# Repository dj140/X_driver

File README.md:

# X_driver
Base on odrive 3.5 sch

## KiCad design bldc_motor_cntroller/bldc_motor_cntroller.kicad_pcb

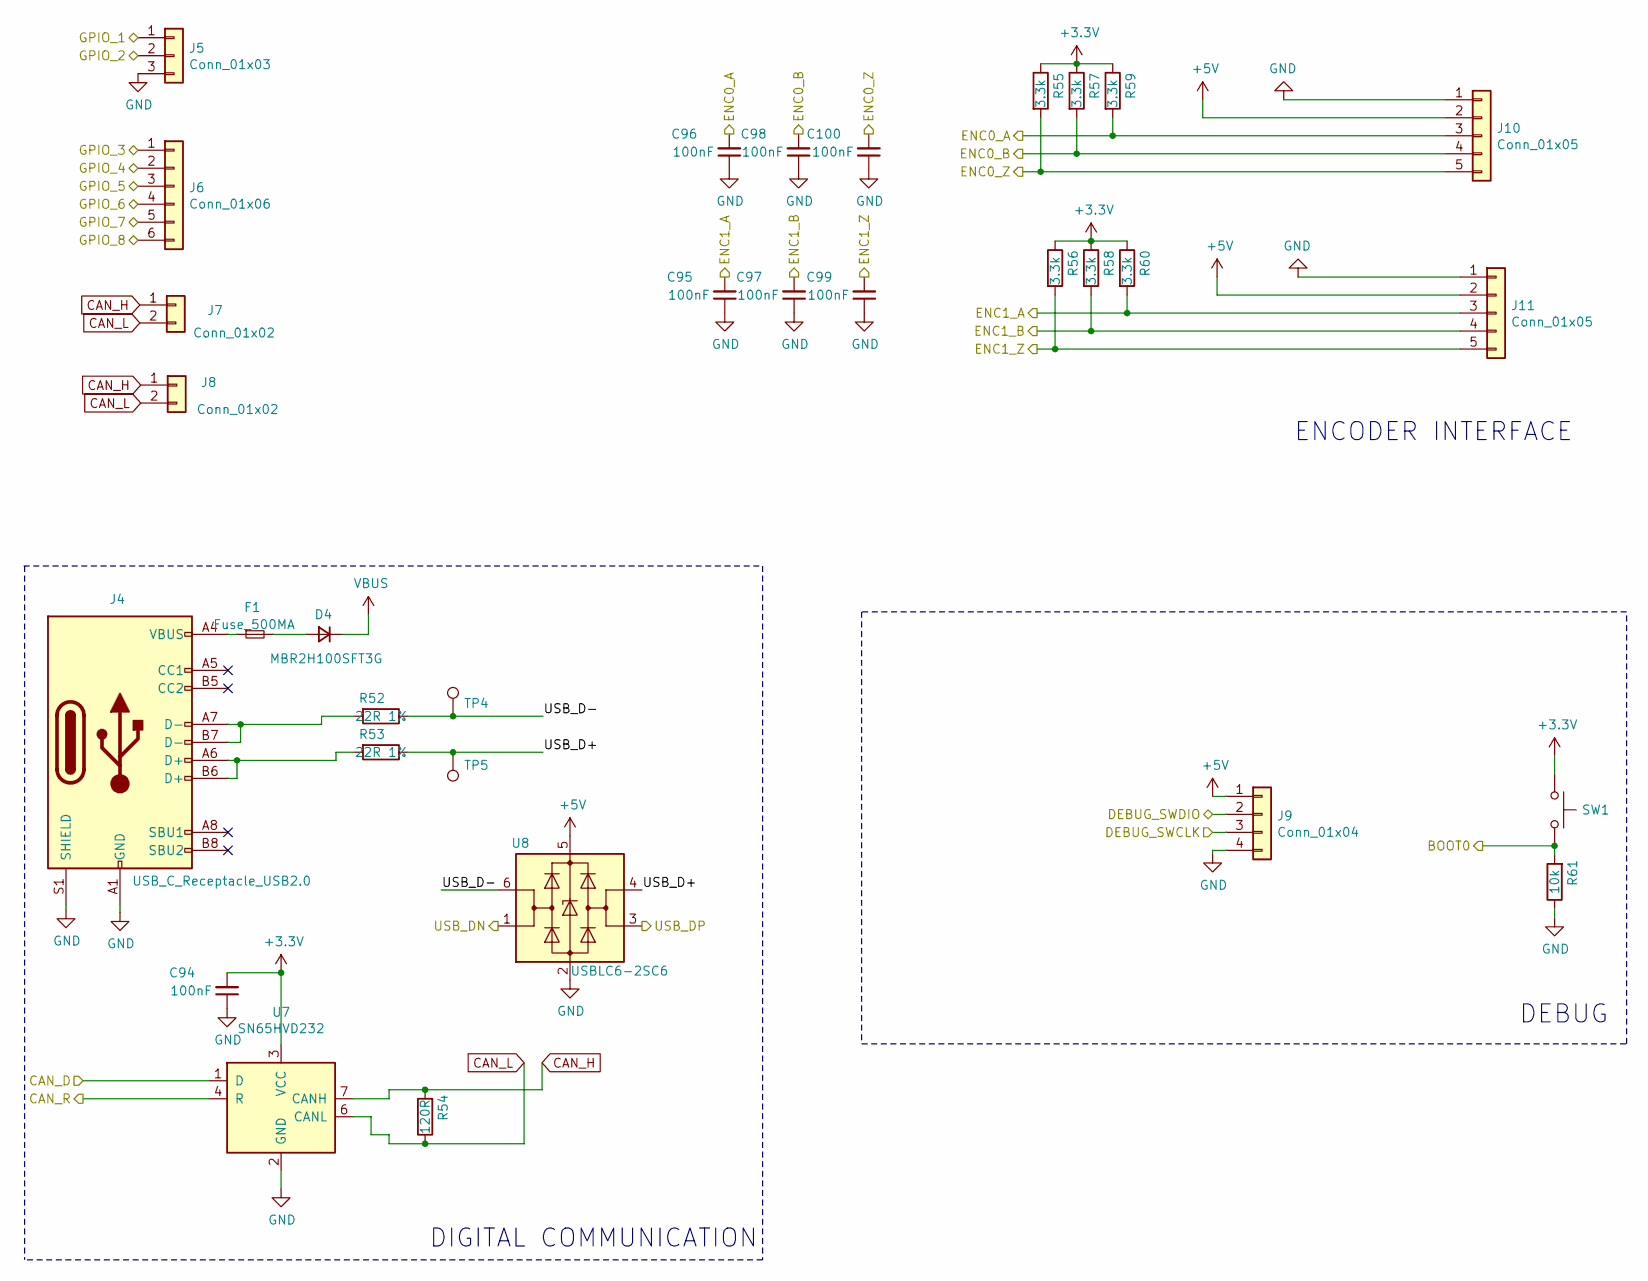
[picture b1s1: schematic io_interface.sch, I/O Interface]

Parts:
C94, C95, C96, C97, C98, C99, C100: 100nF; C_0402_1005Metric; MPN GRM155R62A104KE14D; LCSC Part # C1525
D4: MBR2H100SFT3G; D_SOD-123F
F1: Fuse_500MA; Fuse_1206_3216Metric
J4: USB_C_Receptacle_USB2.0; USB_C_Receptacle_HRO_TYPE-C-31-M-12
J5: Conn_01x03; JST_SH_SM03B-SRSS-TB_1x03-1MP_P1.00mm_Horizontal
J6: Conn_01x06; JST_SH_SM06B-SRSS-TB_1x06-1MP_P1.00mm_Horizontal
J7, J8: Conn_01x02; JST_SH_SM02B-SRSS-TB_1x02-1MP_P1.00mm_Horizontal
J9: Conn_01x04; JST_SH_SM04B-SRSS-TB_1x04-1MP_P1.00mm_Horizontal
J10, J11: Conn_01x05; JST_SH_SM05B-SRSS-TB_1x05-1MP_P1.00mm_Horizontal
R52, R53: 22R 1%; R_0402_1005Metric; MPN CRCW040222R0FKEDC; LCSC Part # C25092
R54: 120R; R_0402_1005Metric; MPN ERJ-2RKF1200X; LCSC Part # C25079
R55, R56, R57, R58, R59, R60: 3.3k; R_0402_1005Metric; MPN CRCW04023K30FKEDC; LCSC Part # C25890
R61: 10k; R_0402_1005Metric; MPN CRCW040210K0FKEDC; LCSC Part # C25744
SW1: B3U-1000P-B; SW_SPST_B3U-1000P; MPN B3U-1000P-B
TP4, TP5: TestPoint; TestPoint_Pad_D1.0mm
U7: SN65HVD232; SOIC-8_3.9x4.9mm_P1.27mm
U8: USBLC6-2SC6; SOT-23-6

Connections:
+3V3: C94.2, R55.1, R56.1, R57.1, R58.1, R59.1, R60.1, SW1.1, U7.3 (VCC); also elsewhere on the board
+5V: D4.1 (K), J9.1, J10.2, J11.2, U8.5 (VBUS); also elsewhere on the board
/I/O Interface/BOOT0: R61.2, SW1.2; also elsewhere on the board
/I/O Interface/CAN_D: U7.1 (D); also elsewhere on the board
/I/O Interface/CAN_R: U7.4 (R); also elsewhere on the board
/I/O Interface/DEBUG_SWCLK: J9.3; also elsewhere on the board
/I/O Interface/DEBUG_SWDIO: J9.2; also elsewhere on the board
/I/O Interface/ENC0_A: C96.2, J10.3, R59.2; also elsewhere on the board
/I/O Interface/ENC0_B: C98.2, J10.4, R57.2; also elsewhere on the board
/I/O Interface/ENC0_Z: C100.2, J10.5, R55.2; also elsewhere on the board
/I/O Interface/ENC1_A: C95.2, J11.3, R60.2; also elsewhere on the board
/I/O Interface/ENC1_B: C97.2, J11.4, R58.2; also elsewhere on the board
/I/O Interface/ENC1_Z: C99.2, J11.5, R56.2; also elsewhere on the board
/I/O Interface/GPIO_1: J5.1; also elsewhere on the board
/I/O Interface/GPIO_2: J5.2; also elsewhere on the board
/I/O Interface/GPIO_3: J6.1; also elsewhere on the board
/I/O Interface/GPIO_4: J6.2; also elsewhere on the board
/I/O Interface/GPIO_5: J6.3; also elsewhere on the board
/I/O Interface/GPIO_6: J6.4; also elsewhere on the board
/I/O Interface/GPIO_7: J6.5; also elsewhere on the board
/I/O Interface/GPIO_8: J6.6; also elsewhere on the board
/I/O Interface/USB_D+: R53.1, TP5.1, U8.4 (I/O2)
/I/O Interface/USB_D-: R52.1, TP4.1, U8.6 (I/O1)
/I/O Interface/USB_DN: U8.1 (I/O1); also elsewhere on the board
/I/O Interface/USB_DP: U8.3 (I/O2); also elsewhere on the board
CAN_H: J7.1, J8.1, R54.2, U7.7 (CANH)
CAN_L: J7.2, J8.2, R54.1, U7.6 (CANL)
GND: C94.1, C95.1, C96.1, C97.1, C98.1, C99.1, C100.1, J4.A1 (GND), J4.A12 (GND), J4.B1 (GND), J4.B12 (GND), J4.S1 (SHIELD), J5.3, J9.4, J10.1, J11.1, R61.1, U7.2 (GND), U8.2 (GND); also elsewhere on the board
unnamed: D4.2 (A), F1.2
unnamed: F1.1, J4.A4 (VBUS), J4.A9 (VBUS), J4.B4 (VBUS), J4.B9 (VBUS)
unnamed: J4.A6 (D+), J4.B6 (D+), R53.2
unnamed: J4.A7 (D-), J4.B7 (D-), R52.2

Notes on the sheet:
DIGITAL COMMUNICATION
DEBUG
ENCODER INTERFACE

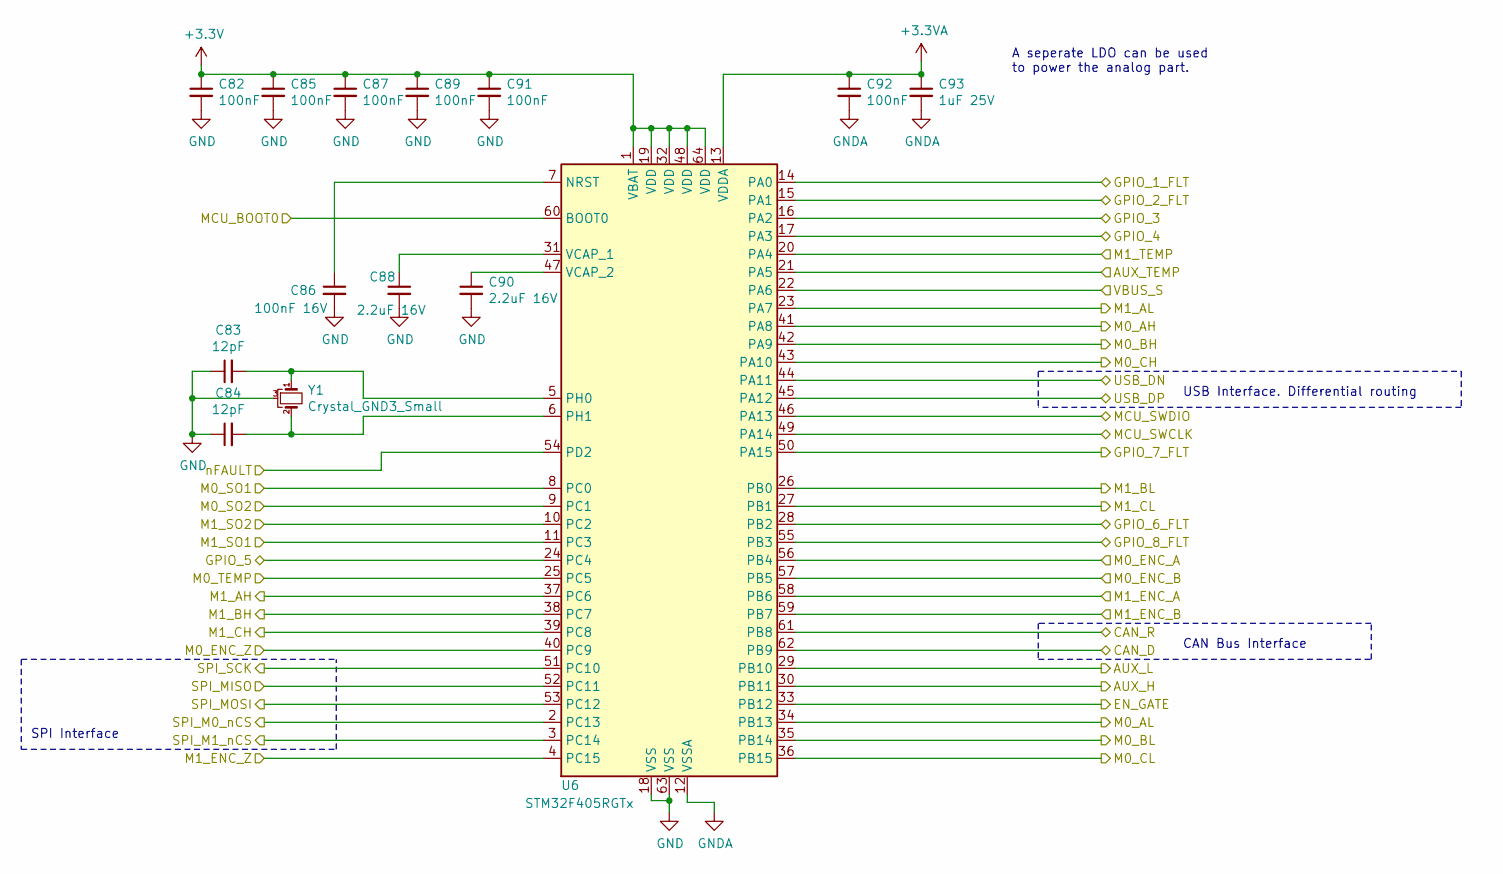
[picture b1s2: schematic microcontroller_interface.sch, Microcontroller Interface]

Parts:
C82, C85, C87, C89, C91, C92: 100nF; C_0402_1005Metric; MPN GRM155R62A104KE14D; LCSC Part # C1525
C83, C84: 12pF; C_0402_1005Metric; MPN GCQ1555C1H120FB01D; LCSC Part # C1547
C86: 100nF 16V; C_0402_1005Metric; MPN GRM155C81E225KE11D; LCSC Part # C1525
C88, C90: 2.2uF 16V; C_0402_1005Metric; MPN GRM155C81E225KE11D
C93: 1uF 25V; C_0402_1005Metric; MPN GMK105CC6105MV-F; LCSC Part # C52923
U6: STM32F405RGTx; LQFP-64_10x10mm_P0.5mm; MPN STM32F405RGT7
Y1: Crystal_GND3_Small; CSTCE8M00G55-R0

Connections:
+3.3VA: C92.1, C93.1, U6.13 (VDDA); also elsewhere on the board
+3V3: C82.1, C85.1, C87.1, C89.1, C91.1, U6.1 (VBAT), U6.19 (VDD), U6.32 (VDD), U6.48 (VDD), U6.64 (VDD); also elsewhere on the board
/I/O Interface/BOOT0: U6.60 (BOOT0); also elsewhere on the board
/I/O Interface/CAN_D: U6.62 (PB9); also elsewhere on the board
/I/O Interface/CAN_R: U6.61 (PB8); also elsewhere on the board
/I/O Interface/DEBUG_SWCLK: U6.49 (PA14); also elsewhere on the board
/I/O Interface/DEBUG_SWDIO: U6.46 (PA13); also elsewhere on the board
/I/O Interface/ENC0_A: U6.56 (PB4); also elsewhere on the board
/I/O Interface/ENC0_B: U6.57 (PB5); also elsewhere on the board
/I/O Interface/ENC0_Z: U6.40 (PC9); also elsewhere on the board
/I/O Interface/ENC1_A: U6.58 (PB6); also elsewhere on the board
/I/O Interface/ENC1_B: U6.59 (PB7); also elsewhere on the board
/I/O Interface/ENC1_Z: U6.4 (PC15); also elsewhere on the board
/I/O Interface/GPIO_1: U6.14 (PA0); also elsewhere on the board
/I/O Interface/GPIO_2: U6.15 (PA1); also elsewhere on the board
/I/O Interface/GPIO_3: U6.16 (PA2); also elsewhere on the board
/I/O Interface/GPIO_4: U6.17 (PA3); also elsewhere on the board
/I/O Interface/GPIO_5: U6.24 (PC4); also elsewhere on the board
/I/O Interface/GPIO_6: U6.28 (PB2); also elsewhere on the board
/I/O Interface/GPIO_7: U6.50 (PA15); also elsewhere on the board
/I/O Interface/GPIO_8: U6.55 (PB3); also elsewhere on the board
/I/O Interface/USB_DN: U6.44 (PA11); also elsewhere on the board
/I/O Interface/USB_DP: U6.45 (PA12); also elsewhere on the board
/Microcontroller Interface/AUX_H: U6.30 (PB11); also elsewhere on the board
/Microcontroller Interface/AUX_L: U6.29 (PB10); also elsewhere on the board
/Microcontroller Interface/AUX_TEMP: U6.21 (PA5); also elsewhere on the board
/Microcontroller Interface/EN_GATE: U6.33 (PB12); also elsewhere on the board
/Microcontroller Interface/M0_AH: U6.41 (PA8); also elsewhere on the board
/Microcontroller Interface/M0_AL: U6.34 (PB13); also elsewhere on the board
/Microcontroller Interface/M0_BH: U6.42 (PA9); also elsewhere on the board
/Microcontroller Interface/M0_BL: U6.35 (PB14); also elsewhere on the board
/Microcontroller Interface/M0_CH: U6.43 (PA10); also elsewhere on the board
/Microcontroller Interface/M0_CL: U6.36 (PB15); also elsewhere on the board
/Microcontroller Interface/M0_TEMP: U6.25 (PC5); also elsewhere on the board
/Microcontroller Interface/M1_AH: U6.37 (PC6); also elsewhere on the board
/Microcontroller Interface/M1_AL: U6.23 (PA7); also elsewhere on the board
/Microcontroller Interface/M1_BH: U6.38 (PC7); also elsewhere on the board
/Microcontroller Interface/M1_BL: U6.26 (PB0); also elsewhere on the board
/Microcontroller Interface/M1_CH: U6.39 (PC8); also elsewhere on the board
/Microcontroller Interface/M1_CL: U6.27 (PB1); also elsewhere on the board
/Microcontroller Interface/M1_TEMP: U6.20 (PA4); also elsewhere on the board
/Microcontroller Interface/SPI_M0_nCS: U6.2 (PC13); also elsewhere on the board
/Microcontroller Interface/SPI_M1_nCS: U6.3 (PC14); also elsewhere on the board
/Microcontroller Interface/SPI_MISO: U6.52 (PC11); also elsewhere on the board
/Microcontroller Interface/SPI_MOSI: U6.53 (PC12); also elsewhere on the board
/Microcontroller Interface/SPI_SCK: U6.51 (PC10); also elsewhere on the board
/Microcontroller Interface/VBUS_S: U6.22 (PA6); also elsewhere on the board
/Microcontroller Interface/nFAULT: U6.54 (PD2); also elsewhere on the board
/Motor Driver/CSENSE_1: U6.8 (PC0); also elsewhere on the board
/Motor Driver/CSENSE_2: U6.9 (PC1); also elsewhere on the board
/Motor_Driver2/CSENSE_1: U6.11 (PC3); also elsewhere on the board
/Motor_Driver2/CSENSE_2: U6.10 (PC2); also elsewhere on the board
GND: C82.2, C83.1, C84.1, C85.2, C86.2, C87.2, C88.2, C89.2, C90.2, C91.2, C92.2, C93.2, U6.12 (VSSA), U6.18 (VSS), U6.63 (VSS), Y1.3; also elsewhere on the board
unnamed: C83.2, U6.5 (PH0), Y1.1
unnamed: C84.2, U6.6 (PH1), Y1.2
unnamed: C86.1, U6.7 (NRST)
unnamed: C88.1, U6.31 (VCAP_1)
unnamed: C90.1, U6.47 (VCAP_2)

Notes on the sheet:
A seperate LDO can be used to power the analog part.
USB Interface. Differential routing
SPI Interface
CAN Bus Interface

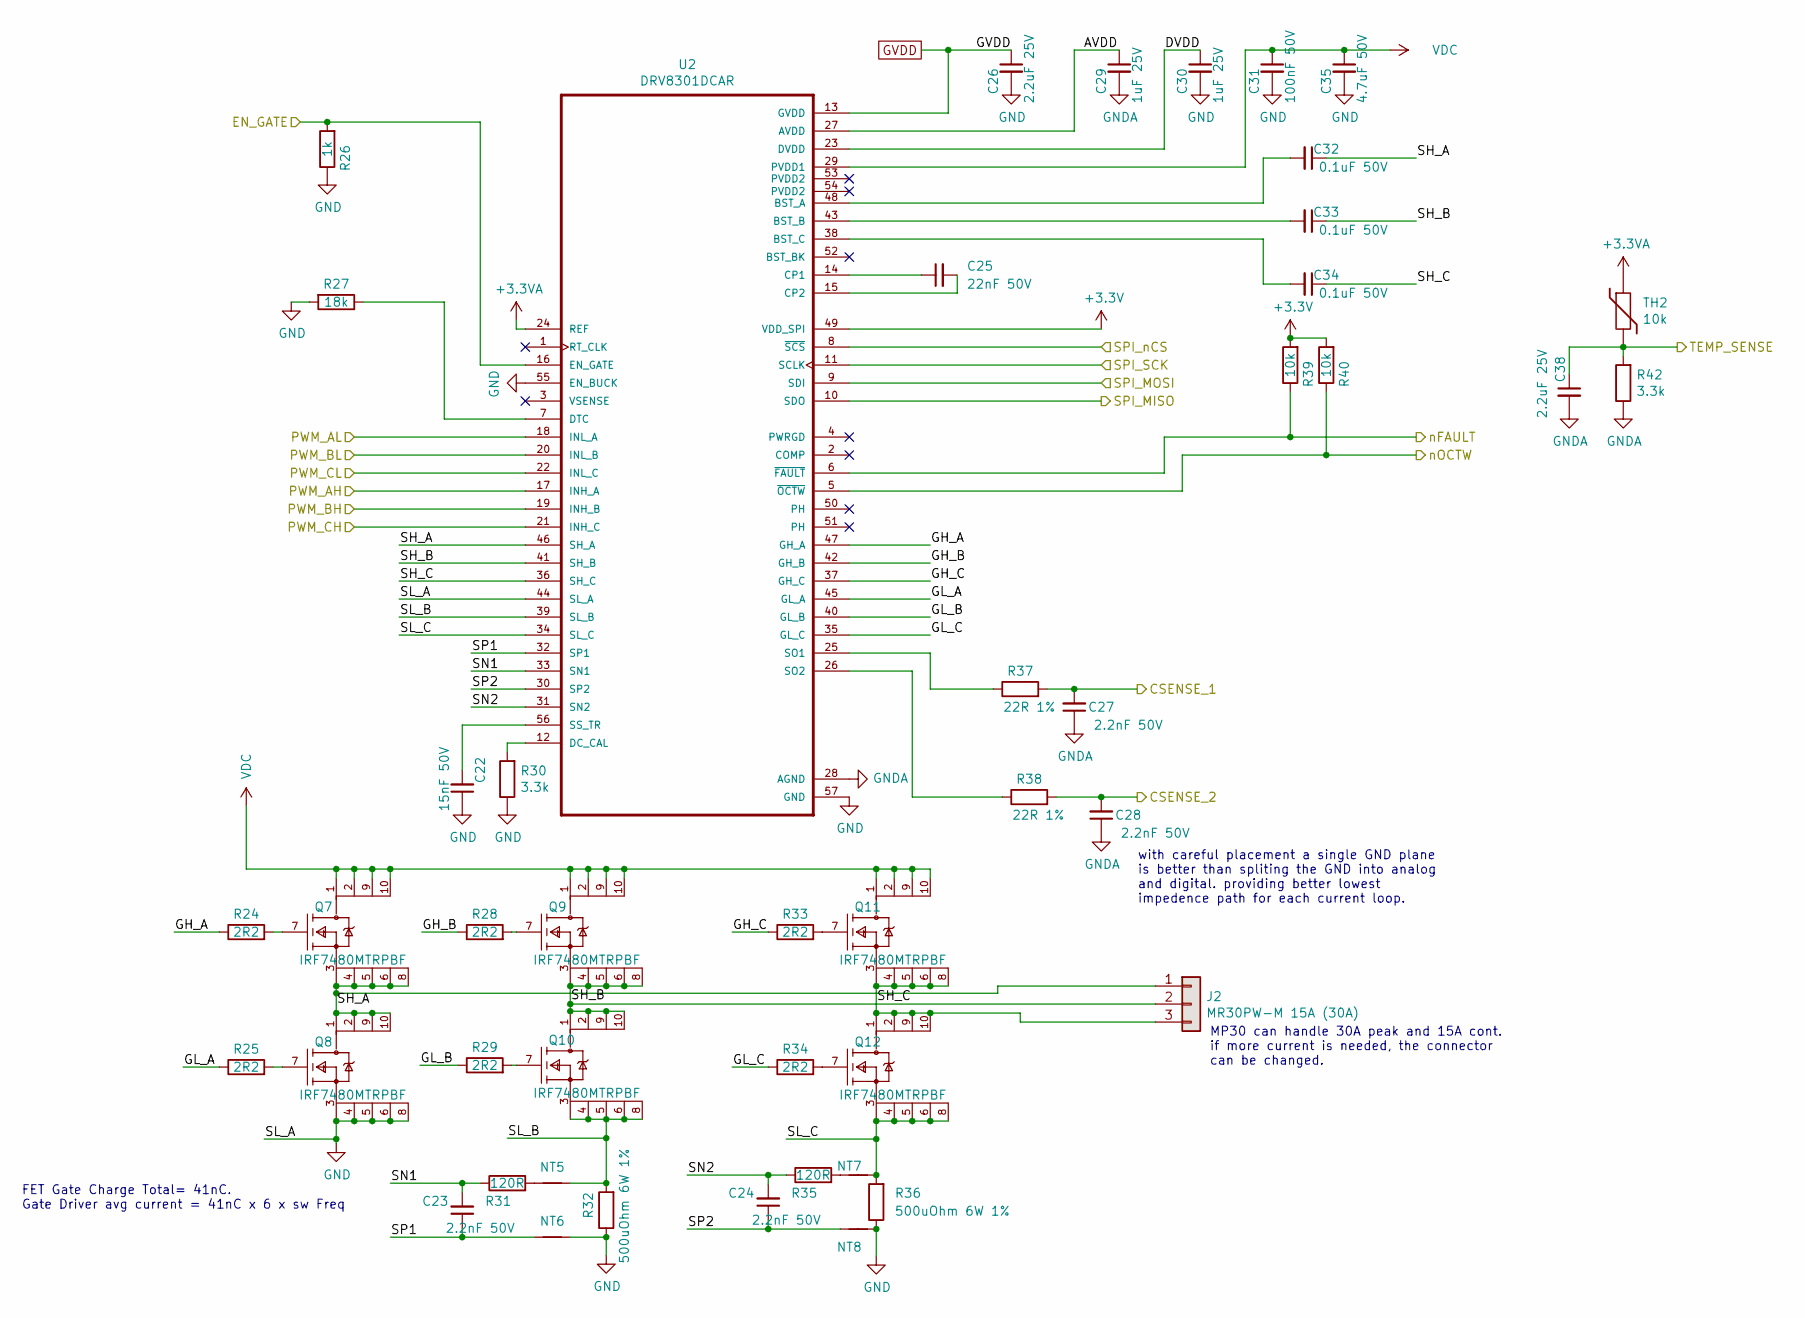
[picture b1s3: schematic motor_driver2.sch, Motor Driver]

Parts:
C22: 15nF 50V; C_0402_1005Metric; MPN GCM155R71E153JA55D
C23, C24, C27, C28: 2.2nF 50V; C_0402_1005Metric; MPN C0402C222J3GEC7411; LCSC Part # C1531
C25: 22nF 50V; C_0402_1005Metric; MPN C0402C223K5REC7411; LCSC Part # C1532
C26, C38: 2.2uF 25V; C_0402_1005Metric; MPN GRM155C81E225KE11D; LCSC Part # C12530
C29, C30: 1uF 25V; C_0402_1005Metric; MPN GMK105CC6105MV-F; LCSC Part # C52923
C31: 100nF 50V; C_0402_1005Metric; MPN GRM155R62A104KE14D
C32, C33, C34: 0.1uF 50V; C_0402_1005Metric; MPN GCM155L8EH104KE07D
C35: 4.7uF 50V; C_1206_3216Metric; MPN HMK325C7475KN-TE
J2: MR30PW-M 15A (30A); AMASS_MR30PW-M_1x03_P3.50mm_Horizontal
NT5, NT6, NT7, NT8: Net-Tie_2; NetTie-2_SMD_Pad0.5mm
Q7, Q8, Q9, Q10, Q11, Q12: IRF7480MTRPBF; Infineon-MG-WDSON-8-05_2016-901-MFG; mouser part number 942-IRF7480MTRPBF; digikey description MOSFET N-CH 40V 217A DIRECTFET
R24, R25, R28, R29, R33, R34: 2R2; R_0402_1005Metric; MPN CRCW04022R20FKEDC
R26: 1k; R_0402_1005Metric; MPN ERJ-2RKF1001X; LCSC Part # C11702
R27: 18k; R_0402_1005Metric; MPN CRCW040218K0FKED; LCSC Part # C25762
R30, R42: 3.3k; R_0402_1005Metric; MPN CRCW04023K30FKEDC; LCSC Part # C25890
R31, R35: 120R; R_0402_1005Metric; MPN ERJ-2RKF1200X; LCSC Part # C25079
R32, R36: 500uOhm 6W 1%; R_2512_6332Metric; MPN CSS2H-2512R-L500F
R37, R38: 22R 1%; R_0402_1005Metric; MPN CRCW040222R0FKEDC; LCSC Part # C25092
R39, R40: 10k; R_0402_1005Metric; MPN CRCW040210K0FKEDC; LCSC Part # C25744
TH2: 10k; R_0402_1005Metric; MPN CRCW040210K0FKEDC
U2: DRV8301DCAR; DRV8301DCA; MPN DRV8301DCAR

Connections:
+3.3VA: TH2.1, U2.24 (REF); also elsewhere on the board
+3V3: R39.2, R40.2, U2.49 (VDD_SPI); also elsewhere on the board
/Microcontroller Interface/EN_GATE: R26.2, U2.16 (EN_GATE); also elsewhere on the board
/Microcontroller Interface/M1_AH: U2.17 (INH_A); also elsewhere on the board
/Microcontroller Interface/M1_AL: U2.18 (INL_A); also elsewhere on the board
/Microcontroller Interface/M1_BH: U2.19 (INH_B); also elsewhere on the board
/Microcontroller Interface/M1_BL: U2.20 (INL_B); also elsewhere on the board
/Microcontroller Interface/M1_CH: U2.21 (INH_C); also elsewhere on the board
/Microcontroller Interface/M1_CL: U2.22 (INL_C); also elsewhere on the board
/Microcontroller Interface/M1_TEMP: C38.1, R42.2, TH2.2; also elsewhere on the board
/Microcontroller Interface/SPI_M1_nCS: U2.8 (~SCS~); also elsewhere on the board
/Microcontroller Interface/SPI_MISO: U2.10 (SDO); also elsewhere on the board
/Microcontroller Interface/SPI_MOSI: U2.9 (SDI); also elsewhere on the board
/Microcontroller Interface/SPI_SCK: U2.11 (SCLK); also elsewhere on the board
/Microcontroller Interface/nFAULT: R39.1, U2.6 (~FAULT~); also elsewhere on the board
/Motor_Driver2/AVDD: C29.1, U2.27 (AVDD)
/Motor_Driver2/CSENSE_1: C27.2, R37.2; also elsewhere on the board
/Motor_Driver2/CSENSE_2: C28.2, R38.2; also elsewhere on the board
/Motor_Driver2/DVDD: C30.1, U2.23 (DVDD)
/Motor_Driver2/GH_A: R24.1, U2.47 (GH_A)
/Motor_Driver2/GH_B: R28.1, U2.42 (GH_B)
/Motor_Driver2/GH_C: R33.1, U2.37 (GH_C)
/Motor_Driver2/GL_A: R25.1, U2.45 (GL_A)
/Motor_Driver2/GL_B: R29.1, U2.40 (GL_B)
/Motor_Driver2/GL_C: R34.1, U2.35 (GL_C)
/Motor_Driver2/SH_A: C32.1, J2.1, Q7.3 (S), Q7.4 (S), Q7.5 (S), Q7.6 (S), Q7.8 (S), Q8.1 (D), Q8.2 (D), Q8.9 (D), Q8.10 (D), U2.46 (SH_A)
/Motor_Driver2/SH_B: C33.1, J2.2, Q9.3 (S), Q9.4 (S), Q9.5 (S), Q9.6 (S), Q9.8 (S), Q10.1 (D), Q10.2 (D), Q10.9 (D), Q10.10 (D), U2.41 (SH_B)
/Motor_Driver2/SH_C: C34.1, J2.3, Q11.3 (S), Q11.4 (S), Q11.5 (S), Q11.6 (S), Q11.8 (S), Q12.1 (D), Q12.2 (D), Q12.9 (D), Q12.10 (D), U2.36 (SH_C)
/Motor_Driver2/SL_B: NT5.2, Q10.3 (S), Q10.4 (S), Q10.5 (S), Q10.6 (S), Q10.8 (S), R32.2, U2.39 (SL_B)
/Motor_Driver2/SL_C: NT7.2, Q12.3 (S), Q12.4 (S), Q12.5 (S), Q12.6 (S), Q12.8 (S), R36.2, U2.34 (SL_C)
/Motor_Driver2/SN1: C23.2, R31.1, U2.33 (SN1)
/Motor_Driver2/SN2: C24.2, R35.1, U2.31 (SN2)
/Motor_Driver2/SP1: C23.1, NT6.1, U2.32 (SP1)
/Motor_Driver2/SP2: C24.1, NT8.1, U2.30 (SP2)
/Motor_Driver2/nOCTW: R40.1, U2.5 (~OCTW~)
GND: C22.1, C26.2, C27.1, C28.1, C29.2, C30.2, C31.2, C35.2, C38.2, NT6.2, NT8.2, Q8.3 (S), Q8.4 (S), Q8.5 (S), Q8.6 (S), Q8.8 (S), R26.1, R27.2, R30.1, R32.1, R36.1, R42.1, U2.28 (AGND), U2.44 (SL_A), U2.55 (EN_BUCK), U2.57 (GND), U2.V; also elsewhere on the board
GVDD: C26.1, U2.13 (GVDD); also elsewhere on the board
unnamed: C22.2, U2.56 (SS_TR)
unnamed: C25.1, U2.14 (CP1)
unnamed: C25.2, U2.15 (CP2)
unnamed: C32.2, U2.48 (BST_A)
unnamed: C33.2, U2.43 (BST_B)
unnamed: C34.2, U2.38 (BST_C)
unnamed: NT5.1, R31.2
unnamed: NT7.1, R35.2
unnamed: Q7.7 (G), R24.2
unnamed: Q8.7 (G), R25.2
unnamed: Q9.7 (G), R28.2
unnamed: Q10.7 (G), R29.2
unnamed: Q11.7 (G), R33.2
unnamed: Q12.7 (G), R34.2
unnamed: R27.1, U2.7 (DTC)
unnamed: R30.2, U2.12 (DC_CAL)
unnamed: R37.1, U2.25 (SO1)
unnamed: R38.1, U2.26 (SO2)
VDC: C31.1, C35.1, Q7.1 (D), Q7.2 (D), Q7.9 (D), Q7.10 (D), Q9.1 (D), Q9.2 (D), Q9.9 (D), Q9.10 (D), Q11.1 (D), Q11.2 (D), Q11.9 (D), Q11.10 (D), U2.29 (PVDD1); also elsewhere on the board

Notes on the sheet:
with careful placement a single GND plane is better than spliting the GND into analog and digital. providing better lowest impedence path for each current loop.
FET Gate Charge Total= 41nC. Gate Driver avg current = 41nC x 6 x sw Freq
MP30 can handle 30A peak and 15A cont. if more current is needed, the connector can be changed.

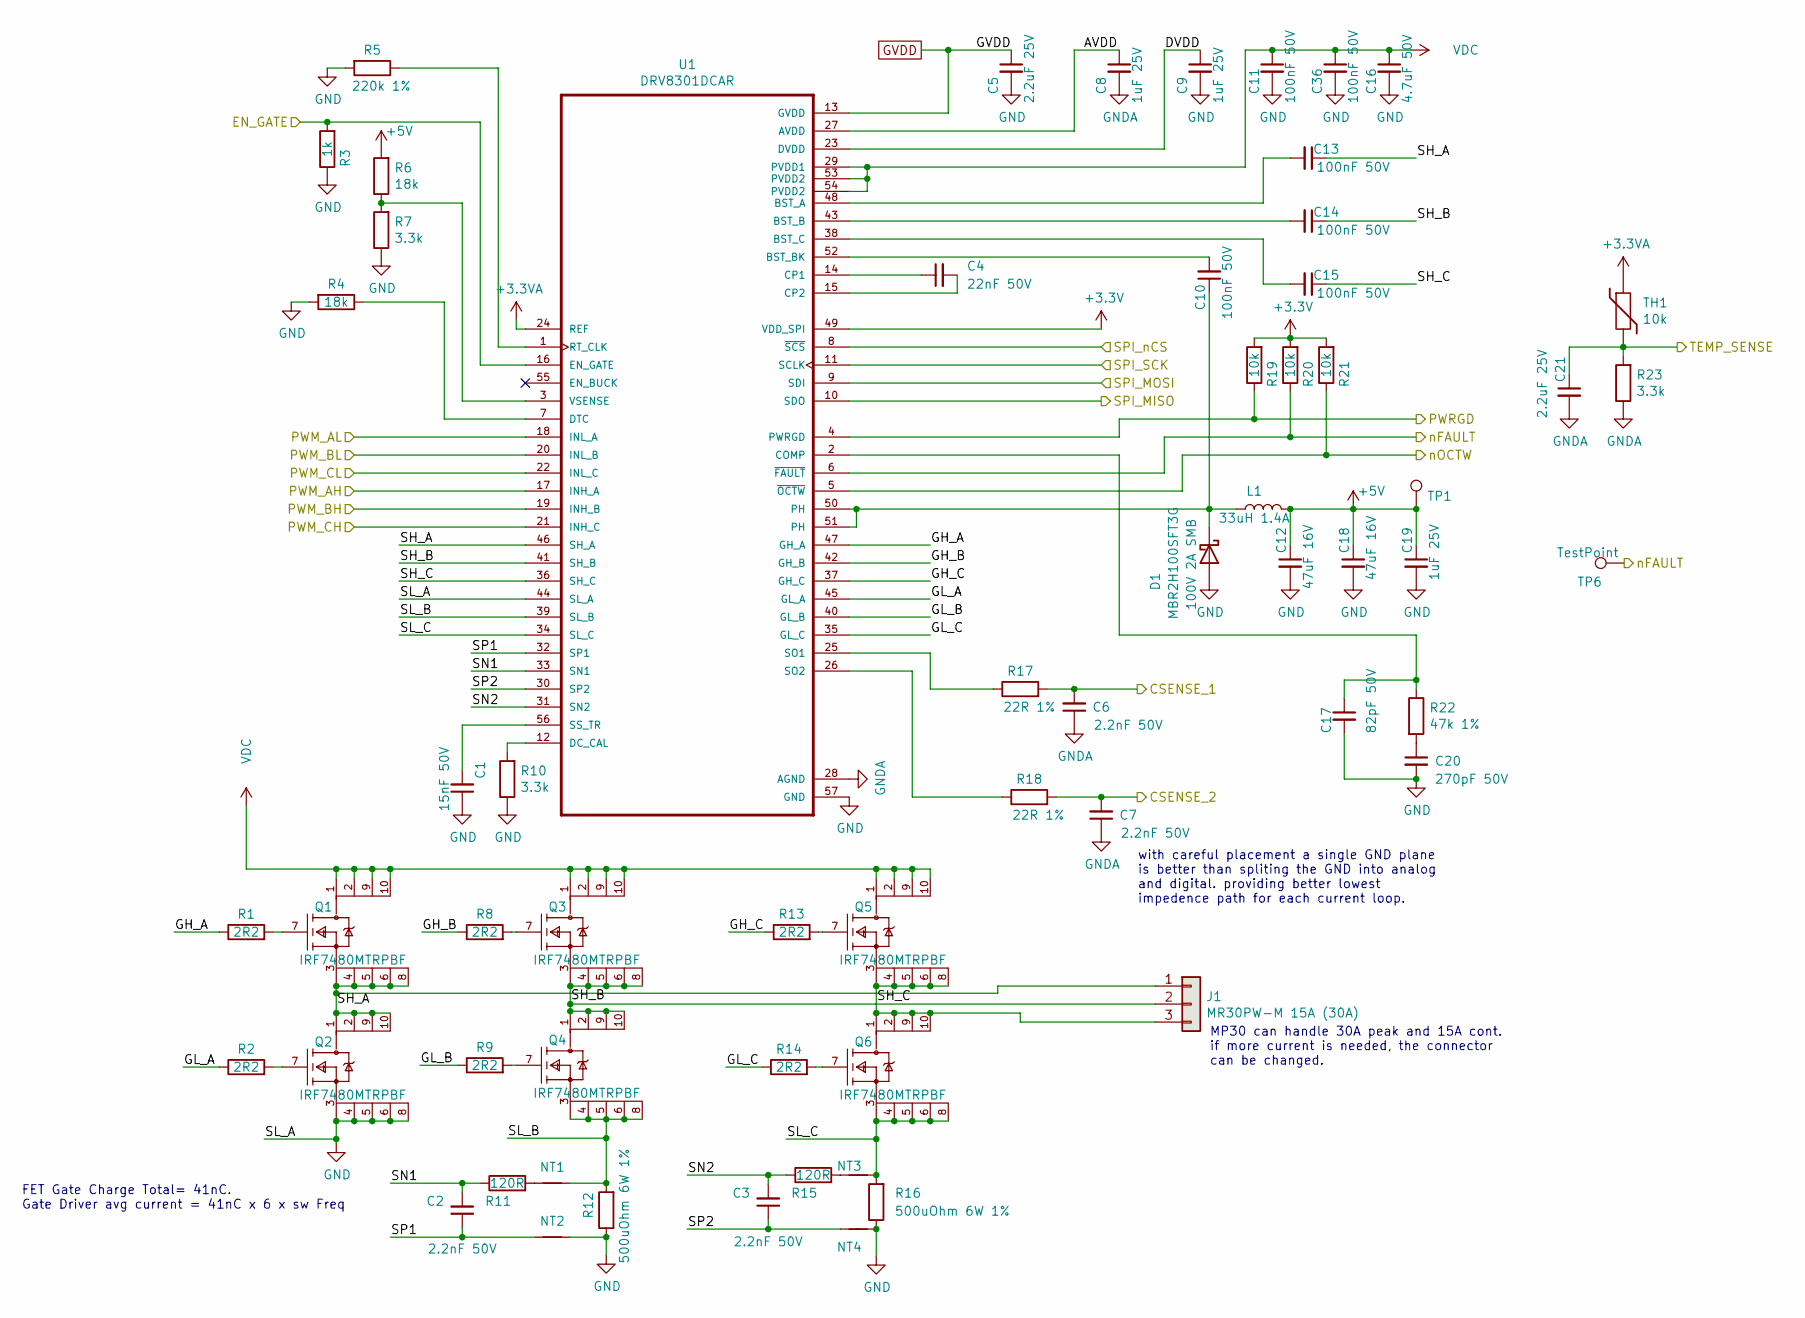
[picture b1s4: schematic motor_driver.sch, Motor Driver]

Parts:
C1: 15nF 50V; C_0402_1005Metric; MPN GCM155R71E153JA55D
C2, C3, C6, C7: 2.2nF 50V; C_0402_1005Metric; MPN C0402C222J3GEC7411; LCSC Part # C1531
C4: 22nF 50V; C_0402_1005Metric; MPN C0402C223K5REC7411; LCSC Part # C1532
C5, C21: 2.2uF 25V; C_0402_1005Metric; MPN GRM155C81E225KE11D; LCSC Part # C12530
C8, C9, C19: 1uF 25V; C_0402_1005Metric; MPN GMK105CC6105MV-F; LCSC Part # C52923
C10, C13, C14, C15: 100nF 50V; C_0402_1005Metric; MPN GCM155L8EH104KE07D
C11, C36: 100nF 50V; C_0402_1005Metric; MPN GRM155R62A104KE14D
C12, C18: 47uF 16V; C_1206_3216Metric; MPN GRM32EC81C476KE15L; LCSC Part # C96123
C16: 4.7uF 50V; C_1206_3216Metric; MPN HMK325C7475KN-TE
C17: 82pF 50V; C_0402_1005Metric; MPN VJ0402A820JXACW1BC
C20: 270pF 50V; C_0402_1005Metric; MPN GRM1555C1H271FA01D
D1: 100V 2A SMB; D_SOD-123F; MPN MBR2H100SFT3G
J1: MR30PW-M 15A (30A); AMASS_MR30PW-M_1x03_P3.50mm_Horizontal
L1: 33uH 1.4A; L_Taiyo-Yuden_NR-60xx; MPN NR6045T330M
NT1, NT2, NT3, NT4: Net-Tie_2; NetTie-2_SMD_Pad0.5mm
Q1, Q2, Q3, Q4, Q5, Q6: IRF7480MTRPBF; Infineon-MG-WDSON-8-05_2016-901-MFG; mouser part number 942-IRF7480MTRPBF; digikey description MOSFET N-CH 40V 217A DIRECTFET
R1, R2, R8, R9, R13, R14: 2R2; R_0402_1005Metric; MPN CRCW04022R20FKEDC
R3: 1k; R_0402_1005Metric; MPN ERJ-2RKF1001X; LCSC Part # C11702
R4, R6: 18k; R_0402_1005Metric; MPN CRCW040218K0FKED; LCSC Part # C25762
R5: 220k 1%; R_0402_1005Metric; MPN CRCW0402220KFKEDC; LCSC Part # C25767
R7, R10, R23: 3.3k; R_0402_1005Metric; MPN CRCW04023K30FKEDC; LCSC Part # C25890
R11, R15: 120R; R_0402_1005Metric; MPN ERJ-2RKF1200X; LCSC Part # C25079
R12, R16: 500uOhm 6W 1%; R_2512_6332Metric; MPN CSS2H-2512R-L500F
R17, R18: 22R 1%; R_0402_1005Metric; MPN CRCW040222R0FKEDC; LCSC Part # C25092
R19, R20, R21: 10k; R_0402_1005Metric; MPN CRCW040210K0FKEDC; LCSC Part # C25744
R22: 47k 1%; R_0402_1005Metric; MPN CRGP0402F47K; LCSC Part # C25792
TH1: 10k; R_0402_1005Metric; MPN CRCW040210K0FKEDC
TP1, TP6: TestPoint; TestPoint_Pad_D1.0mm
U1: DRV8301DCAR; DRV8301DCA; MPN DRV8301DCAR

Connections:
+3.3VA: TH1.1, U1.24 (REF); also elsewhere on the board
+3V3: R19.2, R20.2, R21.2, U1.49 (VDD_SPI); also elsewhere on the board
+5V: C12.1, C18.1, C19.1, L1.2, R6.2, TP1.1; also elsewhere on the board
/Microcontroller Interface/EN_GATE: R3.2, U1.16 (EN_GATE); also elsewhere on the board
/Microcontroller Interface/M0_AH: U1.17 (INH_A); also elsewhere on the board
/Microcontroller Interface/M0_AL: U1.18 (INL_A); also elsewhere on the board
/Microcontroller Interface/M0_BH: U1.19 (INH_B); also elsewhere on the board
/Microcontroller Interface/M0_BL: U1.20 (INL_B); also elsewhere on the board
/Microcontroller Interface/M0_CH: U1.21 (INH_C); also elsewhere on the board
/Microcontroller Interface/M0_CL: U1.22 (INL_C); also elsewhere on the board
/Microcontroller Interface/M0_TEMP: C21.1, R23.2, TH1.2; also elsewhere on the board
/Microcontroller Interface/SPI_M0_nCS: U1.8 (~SCS~); also elsewhere on the board
/Microcontroller Interface/SPI_MISO: U1.10 (SDO); also elsewhere on the board
/Microcontroller Interface/SPI_MOSI: U1.9 (SDI); also elsewhere on the board
/Microcontroller Interface/SPI_SCK: U1.11 (SCLK); also elsewhere on the board
/Microcontroller Interface/nFAULT: R20.1, TP6.1, U1.6 (~FAULT~); also elsewhere on the board
/Motor Driver/AVDD: C8.1, U1.27 (AVDD)
/Motor Driver/CSENSE_1: C6.2, R17.2; also elsewhere on the board
/Motor Driver/CSENSE_2: C7.2, R18.2; also elsewhere on the board
/Motor Driver/DVDD: C9.1, U1.23 (DVDD)
/Motor Driver/GH_A: R1.1, U1.47 (GH_A)
/Motor Driver/GH_B: R8.1, U1.42 (GH_B)
/Motor Driver/GH_C: R13.1, U1.37 (GH_C)
/Motor Driver/GL_A: R2.1, U1.45 (GL_A)
/Motor Driver/GL_B: R9.1, U1.40 (GL_B)
/Motor Driver/GL_C: R14.1, U1.35 (GL_C)
/Motor Driver/PWRGD: R19.1, U1.4 (PWRGD)
/Motor Driver/SH_A: C13.1, J1.1, Q1.3 (S), Q1.4 (S), Q1.5 (S), Q1.6 (S), Q1.8 (S), Q2.1 (D), Q2.2 (D), Q2.9 (D), Q2.10 (D), U1.46 (SH_A)
/Motor Driver/SH_B: C14.1, J1.2, Q3.3 (S), Q3.4 (S), Q3.5 (S), Q3.6 (S), Q3.8 (S), Q4.1 (D), Q4.2 (D), Q4.9 (D), Q4.10 (D), U1.41 (SH_B)
/Motor Driver/SH_C: C15.1, J1.3, Q5.3 (S), Q5.4 (S), Q5.5 (S), Q5.6 (S), Q5.8 (S), Q6.1 (D), Q6.2 (D), Q6.9 (D), Q6.10 (D), U1.36 (SH_C)
/Motor Driver/SL_B: NT1.2, Q4.3 (S), Q4.4 (S), Q4.5 (S), Q4.6 (S), Q4.8 (S), R12.2, U1.39 (SL_B)
/Motor Driver/SL_C: NT3.2, Q6.3 (S), Q6.4 (S), Q6.5 (S), Q6.6 (S), Q6.8 (S), R16.2, U1.34 (SL_C)
/Motor Driver/SN1: C2.2, R11.1, U1.33 (SN1)
/Motor Driver/SN2: C3.2, R15.1, U1.31 (SN2)
/Motor Driver/SP1: C2.1, NT2.1, U1.32 (SP1)
/Motor Driver/SP2: C3.1, NT4.1, U1.30 (SP2)
/Motor Driver/nOCTW: R21.1, U1.5 (~OCTW~)
GND: C1.1, C5.2, C6.1, C7.1, C8.2, C9.2, C11.2, C12.2, C16.2, C17.2, C18.2, C19.2, C20.2, C21.2, C36.2, D1.2 (A), NT2.2, NT4.2, Q2.3 (S), Q2.4 (S), Q2.5 (S), Q2.6 (S), Q2.8 (S), R3.1, R4.2, R5.2, R7.1, R10.1, R12.1, R16.1, R23.1, U1.28 (AGND), U1.44 (SL_A), U1.57 (GND), U1.V; also elsewhere on the board
GVDD: C5.1, U1.13 (GVDD); also elsewhere on the board
unnamed: C1.2, U1.56 (SS_TR)
unnamed: C4.1, U1.14 (CP1)
unnamed: C4.2, U1.15 (CP2)
unnamed: C10.1, D1.1 (K), L1.1, U1.50 (PH), U1.51 (PH)
unnamed: C10.2, U1.52 (BST_BK)
unnamed: C13.2, U1.48 (BST_A)
unnamed: C14.2, U1.43 (BST_B)
unnamed: C15.2, U1.38 (BST_C)
unnamed: C17.1, R22.1, U1.2 (COMP)
unnamed: C20.1, R22.2
unnamed: NT1.1, R11.2
unnamed: NT3.1, R15.2
unnamed: Q1.7 (G), R1.2
unnamed: Q2.7 (G), R2.2
unnamed: Q3.7 (G), R8.2
unnamed: Q4.7 (G), R9.2
unnamed: Q5.7 (G), R13.2
unnamed: Q6.7 (G), R14.2
unnamed: R4.1, U1.7 (DTC)
unnamed: R5.1, U1.1 (RT_CLK)
unnamed: R6.1, R7.2, U1.3 (VSENSE)
unnamed: R10.2, U1.12 (DC_CAL)
unnamed: R17.1, U1.25 (SO1)
unnamed: R18.1, U1.26 (SO2)
VDC: C11.1, C16.1, C36.1, Q1.1 (D), Q1.2 (D), Q1.9 (D), Q1.10 (D), Q3.1 (D), Q3.2 (D), Q3.9 (D), Q3.10 (D), Q5.1 (D), Q5.2 (D), Q5.9 (D), Q5.10 (D), U1.29 (PVDD1), U1.53 (PVDD2), U1.54 (PVDD2); also elsewhere on the board

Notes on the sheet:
with careful placement a single GND plane is better than spliting the GND into analog and digital. providing better lowest impedence path for each current loop.
FET Gate Charge Total= 41nC. Gate Driver avg current = 41nC x 6 x sw Freq
MP30 can handle 30A peak and 15A cont. if more current is needed, the connector can be changed.

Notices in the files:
parts and their libraries:
Copyright 2016 Accelerated Designs. All rights reserved.
